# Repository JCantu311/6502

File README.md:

# 6502
Writing code for the W65C02 microprocessor.

## Links
[Compiler Project](COMPILER.md)

## Experimentation
The project root is dedicated to writing code for testing. The Computer Code subdirectory is for designing code for a custom computer I am designing, while the Computer Designs subdirectory is for the computer itself (including peripherals and extra hardware).

## Designing
The Computer I am designing is purely experimental and is (at the time of writing) far from production.

Further updates in the future could possibly result in a for-production product.

The Computer Code subdirectory contains the source code for the version of MS Basic designed for the computer, the operating system/kernel, and wozmon as a system monitor.

I would not recommend using any of my source code as its very sloppy and written with little competence, however, if you do, you know where to find the terms of the license.

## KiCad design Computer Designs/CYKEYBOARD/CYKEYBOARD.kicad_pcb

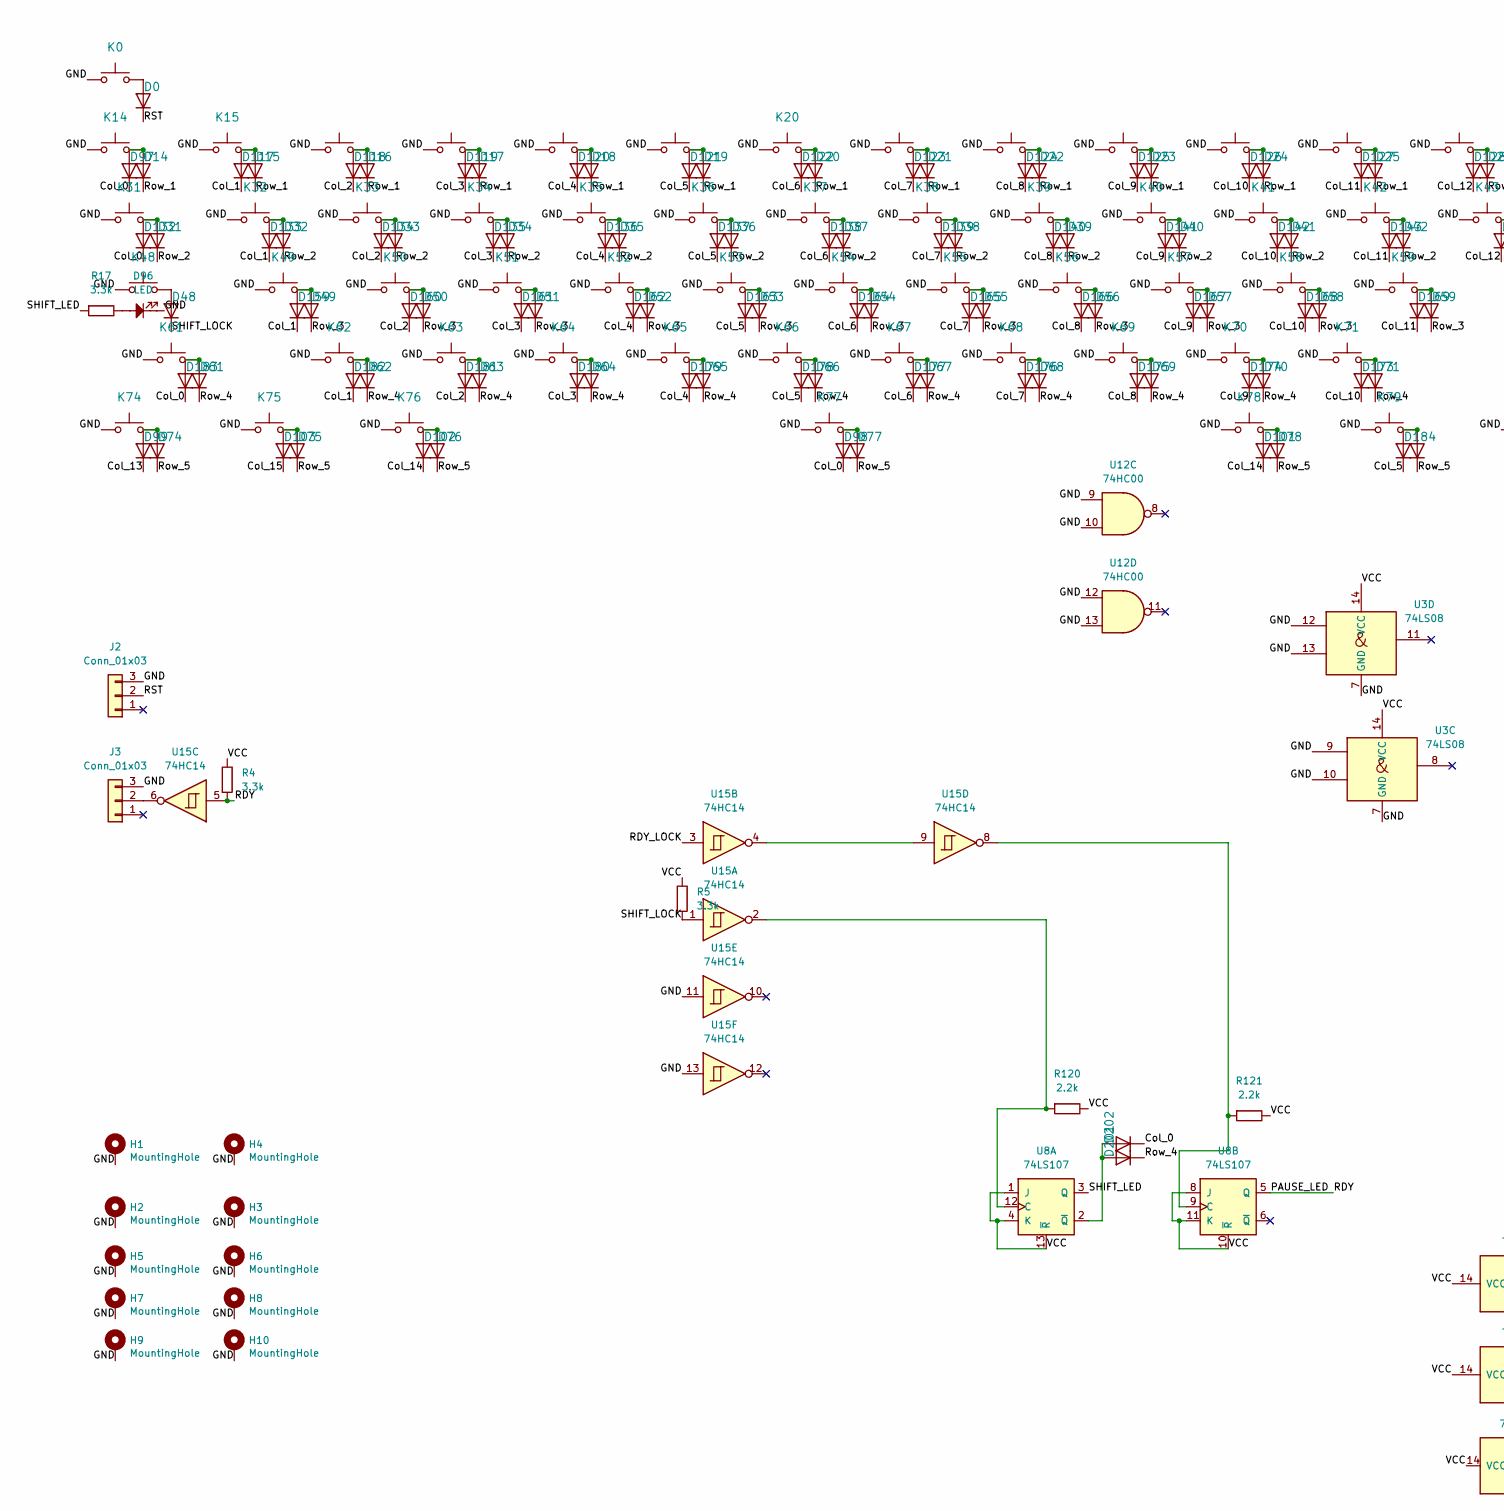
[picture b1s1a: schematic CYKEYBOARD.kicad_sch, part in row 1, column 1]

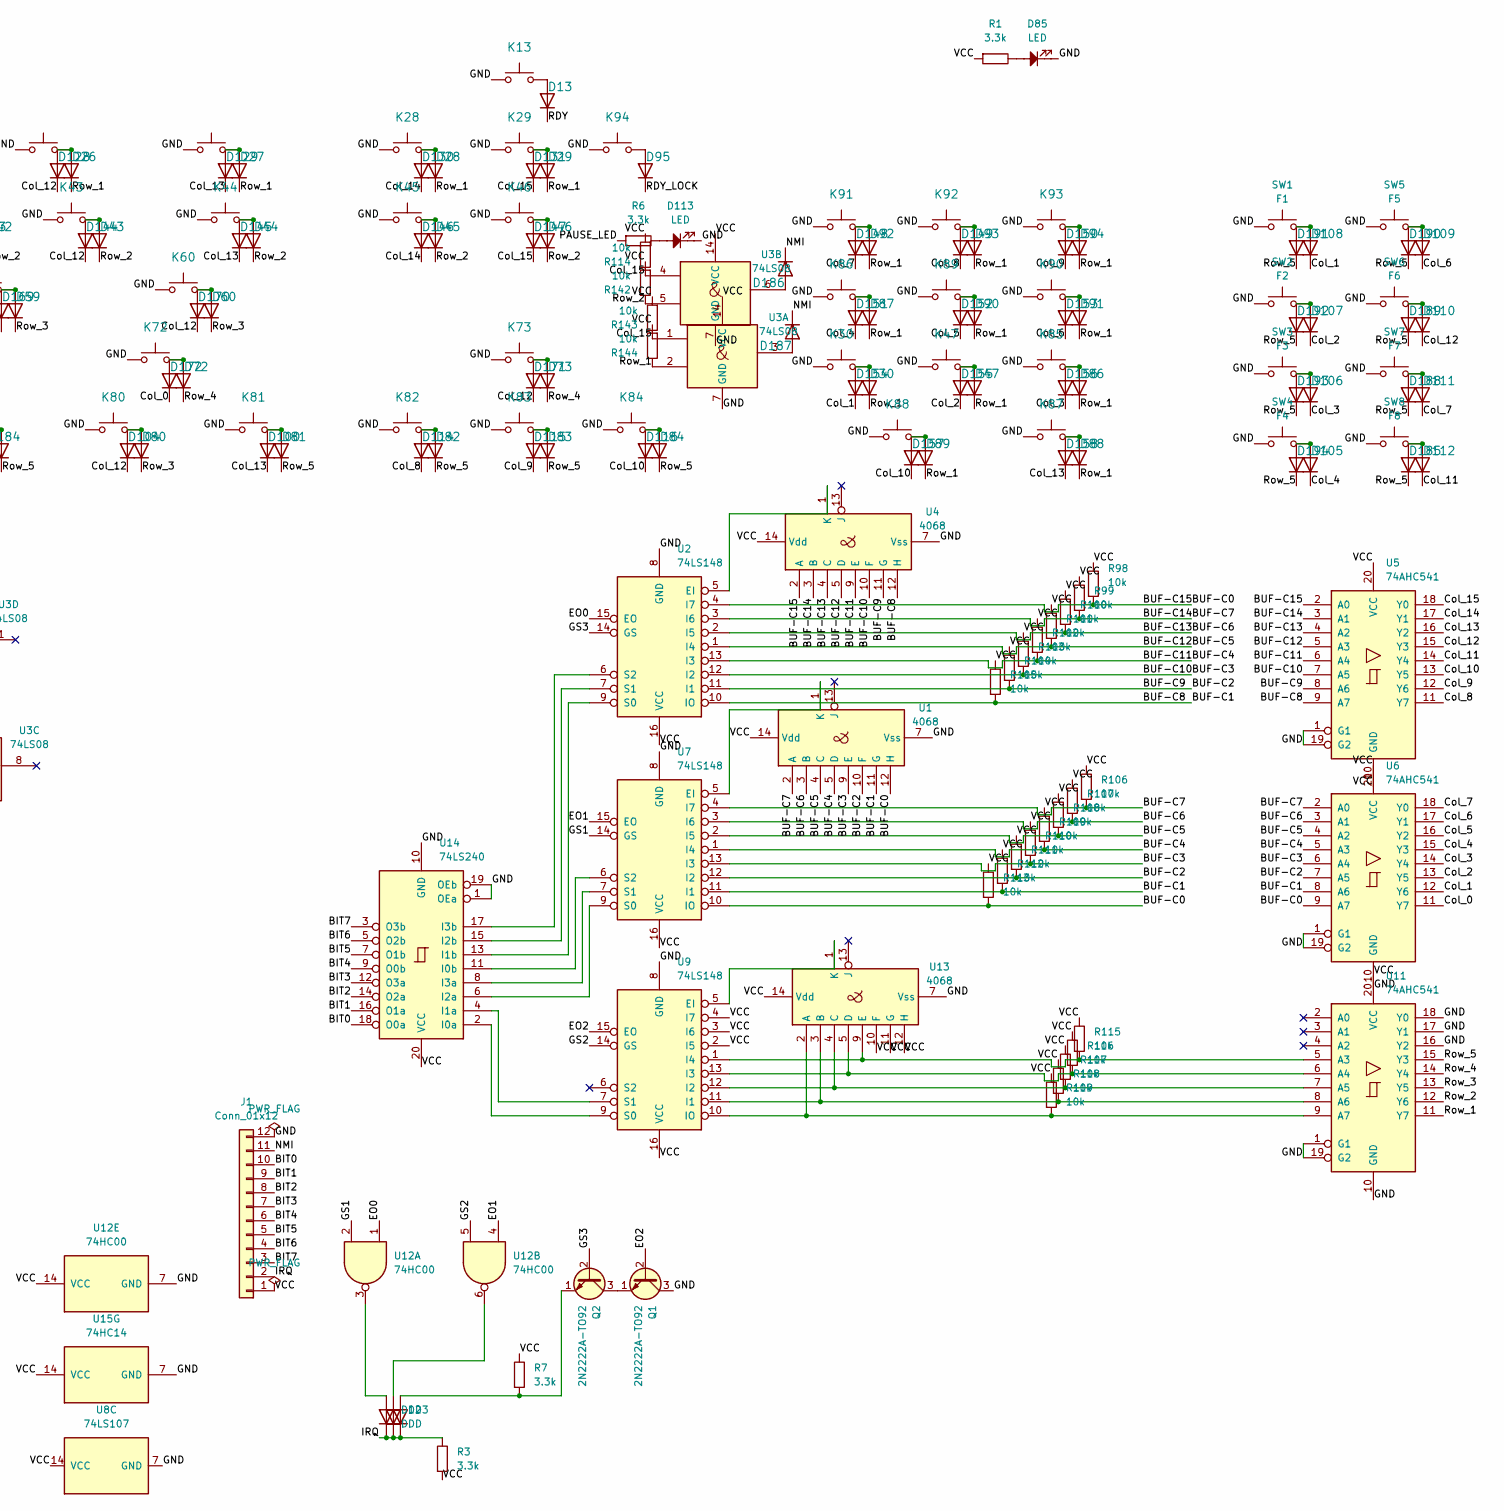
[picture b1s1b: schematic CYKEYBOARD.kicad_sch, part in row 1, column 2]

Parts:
D0, D13, D14, D15, D16, D17, D18, D19, D20, D21, D22, D23, D24, D25, D26, D27, D28, D29, D30, D31, D32, D33, D34, D35, D36, D37, D38, D39, D40, D41, D42, D43, D44, D45, D46, D47, D48, D49, D50, D51, D52, D53, D54, D55, D56, D57, D58, D59, D60, D61, D62, D63, D64, D65, D66, D67, D68, D69, D70, D71, D72, D73, D74, D75, D76, D77, D78, D79, D80, D81, D82, D83, D84, D86, D87, D88, D89, D90, D91, D92, D93, D94, D95, D97, D98, D99, D100, D101, D102, D103, D104, D105, D106, D107, D108, D109, D110, D111, D112, D114, D115, D116, D117, D118, D119, D120, D121, D122, D123, D124, D125, D126, D127, D128, D129, D130, D131, D132, D133, D134, D135, D136, D137, D138, D139, D140, D141, D142, D143, D144, D145, D146, D147, D148, D149, D150, D151, D152, D153, D154, D155, D156, D157, D158, D159, D160, D161, D162, D163, D164, D165, D166, D167, D168, D169, D170, D171, D172, D173, D174, D175, D176, D177, D178, D179, D180, D181, D182, D183, D184, D185, D186, D187, D188, D189, D190, D191, D192, D193, D194, D201, D202: D; D_T-1_P5.08mm_Horizontal
D1, D2, D3: D; D_DO-35_SOD27_P7.62mm_Horizontal
D85, D96, D113: LED; LED_D5.0mm
H1, H2, H3, H4, H5, H6, H7, H8, H9, H10: MountingHole; MountingHole_2.2mm_M2_Pad_Via
J1: Conn_01x12; PinHeader_1x12_P2.54mm_Vertical
J2, J3: Conn_01x03; FanPinHeader_1x03_P2.54mm_Vertical
K0: RESET; SW_Cherry_MX_1.00u_PCB
K13: READY; SW_Cherry_MX_2.75u_PCB
K14: ~~,,,,,,`; SW_Cherry_MX_1.00u_PCB
K15, K30: !,,,,,,1; SW_Cherry_MX_1.00u_PCB
K16, K47: @,,,,,,2; SW_Cherry_MX_1.00u_PCB
K17, K85: #,,,,,,3; SW_Cherry_MX_1.00u_PCB
K18, K86: $,,,,,,4; SW_Cherry_MX_1.00u_PCB
K19, K89: %,,,,,,5; SW_Cherry_MX_1.00u_PCB
K20, K90: ^,,,,,,6; SW_Cherry_MX_1.00u_PCB
K21, K91: &,,,,,,7; SW_Cherry_MX_1.00u_PCB
K22, K92: *,,,,,,8; SW_Cherry_MX_1.00u_PCB
K23, K93: (,,,,,,9; SW_Cherry_MX_1.00u_PCB
K24: ),,,,,,0; SW_Cherry_MX_1.00u_PCB
K25: _,,,,,,-; SW_Cherry_MX_1.00u_PCB
K26: +,,,,,,=; SW_Cherry_MX_1.00u_PCB
K27: BACKSPACE; SW_Cherry_MX_2.00u_PCB
K28: HOME; SW_Cherry_MX_1.00u_PCB
K29: MON; SW_Cherry_MX_1.00u_PCB
K31: SAVE,,,,,,LOAD; SW_Cherry_MX_1.25u_PCB
K32: Q; SW_Cherry_MX_1.00u_PCB
K33: W; SW_Cherry_MX_1.00u_PCB
K34: E; SW_Cherry_MX_1.00u_PCB
K35: R; SW_Cherry_MX_1.00u_PCB
K36: T; SW_Cherry_MX_1.00u_PCB
K37: Y; SW_Cherry_MX_1.00u_PCB
K38: U; SW_Cherry_MX_1.00u_PCB
K39: I; SW_Cherry_MX_1.00u_PCB
K40: O; SW_Cherry_MX_1.00u_PCB
K41: P; SW_Cherry_MX_1.00u_PCB
K42: {,,,,,,[; SW_Cherry_MX_1.00u_PCB
K43: },,,,,,]; SW_Cherry_MX_1.00u_PCB
K44: |,,,,,,\; SW_Cherry_MX_1.75u_PCB
K45: DEL; SW_Cherry_MX_1.00u_PCB
K46: BAS; SW_Cherry_MX_1.00u_PCB
K48: SHIFT,,,,,,LOCK; SW_Cherry_MX_1.50u_PCB
K49: A; SW_Cherry_MX_1.00u_PCB
K50: S; SW_Cherry_MX_1.00u_PCB
K51: D; SW_Cherry_MX_1.00u_PCB
K52: F; SW_Cherry_MX_1.00u_PCB
K53: G; SW_Cherry_MX_1.00u_PCB
K54: H; SW_Cherry_MX_1.00u_PCB
K55: J; SW_Cherry_MX_1.00u_PCB
K56: K; SW_Cherry_MX_1.00u_PCB
K57: L; SW_Cherry_MX_1.00u_PCB
K58: :,,,,,,;; SW_Cherry_MX_1.00u_PCB
K59: ",,,,,,'; SW_Cherry_MX_1.00u_PCB
K60: ENTER; SW_Cherry_MX_2.25u_PCB
K61: SHIFT; SW_Cherry_MX_2.00u_PCB
K62: Z; SW_Cherry_MX_1.00u_PCB
K63: X; SW_Cherry_MX_1.00u_PCB
K64: C; SW_Cherry_MX_1.00u_PCB
K65: V; SW_Cherry_MX_1.00u_PCB
K66: B; SW_Cherry_MX_1.00u_PCB
K67: N; SW_Cherry_MX_1.00u_PCB
K68: M; SW_Cherry_MX_1.00u_PCB
K69: <,,,,,,,; SW_Cherry_MX_1.00u_PCB
K70: >,,,,,,.; SW_Cherry_MX_1.00u_PCB
K71: ?,,,,,,/; SW_Cherry_MX_1.00u_PCB
K72: SHIFT; SW_Cherry_MX_2.75u_PCB
K73: ^; SW_Cherry_MX_1.00u_PCB
K74, K81: CTRL; SW_Cherry_MX_1.25u_PCB
K75: CYKA,,,,,,TECH; SW_Cherry_MX_1.25u_PCB
K76, K78: ALT; SW_Cherry_MX_1.25u_PCB
K77: Blank; SW_Cherry_MX_6.25u_PCB
K79: FN; SW_Cherry_MX_1.25u_PCB
K80: SELECT; SW_Cherry_MX_1.25u_PCB
K82: <; SW_Cherry_MX_1.00u_PCB
K83: \/; SW_Cherry_MX_1.00u_PCB
K84: >; SW_Cherry_MX_1.00u_PCB
K87: BACKSPACE; SW_Cherry_MX_1.00u_PCB
K88: ),,,,,,0; SW_Cherry_MX_2.00u_PCB
K94: PAUSE; SW_Cherry_MX_1.00u_PCB
Q1, Q2: 2N2222A-TO92; TO-92_Inline_Wide_EBC
R1, R3, R4, R5, R6, R7, R17: 3.3k; R_Axial_DIN0207_L6.3mm_D2.5mm_P10.16mm_Horizontal
R98, R99, R100, R101, R102, R103, R104, R105, R106, R107, R108, R109, R110, R111, R112, R113, R114, R115, R116, R117, R118, R119, R142, R143, R144: 10k; R_Axial_DIN0207_L6.3mm_D2.5mm_P10.16mm_Horizontal
R120, R121: 2.2k; R_Axial_DIN0207_L6.3mm_D2.5mm_P10.16mm_Horizontal
SW1: F1; SW_Cherry_MX_2.00u_PCB
SW2: F2; SW_Cherry_MX_2.00u_PCB
SW3: F3; SW_Cherry_MX_2.00u_PCB
SW4: F4; SW_Cherry_MX_2.00u_PCB
SW5: F5; SW_Cherry_MX_2.00u_PCB
SW6: F6; SW_Cherry_MX_2.00u_PCB
SW7: F7; SW_Cherry_MX_2.00u_PCB
SW8: F8; SW_Cherry_MX_2.00u_PCB
U1, U4, U13: 4068; DIP-14_W7.62mm_Socket
U2, U7, U9: 74LS148; DIP-16_W7.62mm_Socket
U3: 74LS08; DIP-14_W7.62mm_Socket
U5, U6, U11: 74AHC541; DIP-20_W7.62mm_Socket
U8: 74LS107; DIP-14_W7.62mm_Socket
U12: 74HC00; DIP-14_W7.62mm_Socket
U14: 74LS240; DIP-20_W7.62mm_Socket
U15: 74HC14; DIP-14_W7.62mm_Socket

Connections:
/BIT0: J1.10, U14.18 (O0a)
/BIT1: J1.9, U14.16 (O1a)
/BIT2: J1.8, U14.14 (O2a)
/BIT3: J1.7, U14.12 (O3a)
/BIT4: J1.6, U14.9 (O0b)
/BIT5: J1.5, U14.7 (O1b)
/BIT6: J1.4, U14.5 (O2b)
/BIT7: J1.3, U14.3 (O3b)
/BUF-C0: R98.1, R113.1, U1.12 (H), U2.4 (I7), U4.2 (A), U5.2 (A0), U6.9 (A7), U7.10 (IO)
/BUF-C1: R105.1, R112.1, U1.11 (G), U2.10 (IO), U4.12 (H), U5.9 (A7), U6.8 (A6), U7.11 (I1)
/BUF-C2: R104.1, R111.1, U1.10 (F), U2.11 (I1), U4.11 (G), U5.8 (A6), U6.7 (A5), U7.12 (I2)
/BUF-C10: R103.1, R110.1, U1.9 (E), U2.12 (I2), U4.10 (F), U5.7 (A5), U6.6 (A4), U7.13 (I3)
/BUF-C11: R102.1, R109.1, U1.5 (D), U2.13 (I3), U4.9 (E), U5.6 (A4), U6.5 (A3), U7.1 (I4)
/BUF-C12: R101.1, R108.1, U1.4 (C), U2.1 (I4), U4.5 (D), U5.5 (A3), U6.4 (A2), U7.2 (I5)
/BUF-C13: R100.1, R107.1, U1.3 (B), U2.2 (I5), U4.4 (C), U5.4 (A2), U6.3 (A1), U7.3 (I6)
/BUF-C14: R99.1, R106.1, U1.2 (A), U2.3 (I6), U4.3 (B), U5.3 (A1), U6.2 (A0), U7.4 (I7)
/Col_0: D97.1 (K), D98.1 (K), D132.1 (K), D172.1 (K), D183.1 (K), D202.1 (K), U6.11 (Y7)
/Col_1: D108.1 (K), D117.1 (K), D133.1 (K), D154.1 (K), D159.1 (K), D182.1 (K), U6.12 (Y6)
/Col_2: D107.1 (K), D118.1 (K), D134.1 (K), D155.1 (K), D160.1 (K), D181.1 (K), U6.13 (Y5)
/Col_3: D106.1 (K), D119.1 (K), D135.1 (K), D156.1 (K), D161.1 (K), D180.1 (K), U6.14 (Y4)
/Col_4: D105.1 (K), D120.1 (K), D136.1 (K), D151.1 (K), D162.1 (K), D179.1 (K), U6.15 (Y3)
/Col_5: D121.1 (K), D137.1 (K), D152.1 (K), D163.1 (K), D178.1 (K), D184.1 (K), U6.16 (Y2)
/Col_6: D109.1 (K), D122.1 (K), D138.1 (K), D153.1 (K), D164.1 (K), D177.1 (K), U6.17 (Y1)
/Col_7: D111.1 (K), D123.1 (K), D139.1 (K), D148.1 (K), D165.1 (K), D176.1 (K), U6.18 (Y0)
/Col_8: D114.1 (K), D124.1 (K), D140.1 (K), D149.1 (K), D166.1 (K), D175.1 (K), U5.11 (Y7)
/Col_9: D115.1 (K), D125.1 (K), D141.1 (K), D150.1 (K), D167.1 (K), D174.1 (K), U5.12 (Y6)
/Col_10: D116.1 (K), D126.1 (K), D142.1 (K), D157.1 (K), D168.1 (K), D173.1 (K), U5.13 (Y5)
/Col_11: D112.1 (K), D127.1 (K), D143.1 (K), D169.1 (K), U5.14 (Y4)
/Col_12: D104.1 (K), D110.1 (K), D128.1 (K), D144.1 (K), D170.1 (K), D171.1 (K), U5.15 (Y3)
/Col_13: D99.1 (K), D100.1 (K), D129.1 (K), D145.1 (K), D158.1 (K), U5.16 (Y2)
/Col_14: D101.1 (K), D102.1 (K), D130.1 (K), D146.1 (K), U5.17 (Y1)
/Col_15: D103.1 (K), D131.1 (K), D147.1 (K), R114.2, R143.2, U3.1, U3.4, U5.18 (Y0)
/EO0: U2.15 (EO), U12.1
/EO1: U7.15 (EO), U12.4
/EO2: Q1.2 (B), U9.15 (EO)
/GND: D85.1, D96.1, D113.1, H1.1 (1_1), H2.1 (1_1), H3.1 (1_1), H4.1 (1_1), H5.1 (1_1), H6.1 (1_1), H7.1 (1_1), H8.1 (1_1), H9.1 (1_1), H10.1 (1_1), J1.12, J2.3, J3.3, K0.1, K13.1, K14.1, K15.1, K16.1, K17.1, K18.1, K19.1, K20.1, K21.1, K22.1, K23.1, K24.1, K25.1, K26.1, K27.1, K28.1, K29.1, K30.1, K31.1, K32.1, K33.1, K34.1, K35.1, K36.1, K37.1, K38.1, K39.1, K40.1, K41.1, K42.1, K43.1, K44.1, K45.1, K46.1, K47.1, K48.1, K49.1, K50.1, K51.1, K52.1, K53.1, K54.1, K55.1, K56.1, K57.1, K58.1, K59.1, K60.1, K61.1, K62.1, K63.1, K64.1, K65.1, K66.1, K67.1, K68.1, K69.1, K70.1, K71.1, K72.1, K73.1, K74.1, K75.1, K76.1, K77.1, K78.1, K79.1, K80.1, K81.1, K82.1, K83.1, K84.1, K85.1, K86.1, K87.1, K88.1, K89.1, K90.1, K91.1, K92.1, K93.1, K94.1, Q1.3 (C), SW1.1, SW2.1, SW3.1, SW4.1, SW5.1, SW6.1, SW7.1, SW8.1, U1.7 (Vss), U2.8 (GND), U3.7 (GND), U3.9, U3.10, U3.12, U3.13, U4.7 (Vss), U5.1 (G1), U5.19 (G2), U6.1 (G1), U6.10 (GND), U6.19 (G2), U7.8 (GND), U8.7 (GND), U9.8 (GND), U11.1 (G1), U11.10 (GND), U11.16 (Y2), U11.17 (Y1), U11.18 (Y0), U11.19 (G2), U12.7 (GND), U12.9, U12.10, U12.12, U12.13, U13.7 (Vss), U14.1 (OEa), U14.10 (GND), U14.19 (OEb), U15.7 (GND), U15.11, U15.13
/GS1: U7.14 (GS), U12.2
/GS2: U9.14 (GS), U12.5
/GS3: Q2.2 (B), U2.14 (GS)
/IRQ: D1.1 (K), D2.1 (K), D3.1 (K), J1.2, R3.2
/NMI: D186.1 (K), D187.1 (K), J1.11
/PAUSE_LED: D13.1 (K), R4.1, R6.1, U8.5 (Q), U15.5
/RDY_LOCK: D95.1 (K), U15.3
/RST: D0.1 (K), J2.2
/Row_1: D14.1 (K), D15.1 (K), D16.1 (K), D17.1 (K), D18.1 (K), D19.1 (K), D20.1 (K), D21.1 (K), D22.1 (K), D23.1 (K), D24.1 (K), D25.1 (K), D26.1 (K), D27.1 (K), D28.1 (K), D29.1 (K), D30.1 (K), D47.1 (K), D86.1 (K), D87.1 (K), D88.1 (K), D89.1 (K), D90.1 (K), D91.1 (K), D92.1 (K), D93.1 (K), D94.1 (K), R144.2, U3.2, U11.11 (Y7)
/Row_2: D31.1 (K), D32.1 (K), D33.1 (K), D34.1 (K), D35.1 (K), D36.1 (K), D37.1 (K), D38.1 (K), D39.1 (K), D40.1 (K), D41.1 (K), D42.1 (K), D43.1 (K), D44.1 (K), D45.1 (K), D46.1 (K), R142.2, U3.5, U11.12 (Y6)
/Row_3: D49.1 (K), D50.1 (K), D51.1 (K), D52.1 (K), D53.1 (K), D54.1 (K), D55.1 (K), D56.1 (K), D57.1 (K), D58.1 (K), D59.1 (K), D60.1 (K), D80.1 (K), U11.13 (Y5)
/Row_4: D61.1 (K), D62.1 (K), D63.1 (K), D64.1 (K), D65.1 (K), D66.1 (K), D67.1 (K), D68.1 (K), D69.1 (K), D70.1 (K), D71.1 (K), D72.1 (K), D73.1 (K), D201.1 (K), U11.14 (Y4)
/Row_5: D74.1 (K), D75.1 (K), D76.1 (K), D77.1 (K), D78.1 (K), D79.1 (K), D81.1 (K), D82.1 (K), D83.1 (K), D84.1 (K), D185.1 (K), D188.1 (K), D189.1 (K), D190.1 (K), D191.1 (K), D192.1 (K), D193.1 (K), D194.1 (K), U11.15 (Y3)
/SHIFT_LED: R17.1, U8.3 (Q)
/SHIFT_LOCK: D48.1 (K), R5.1, U15.1
/VCC: J1.1, R1.1, R3.1, R4.2, R5.2, R7.2, R98.2, R99.2, R100.2, R101.2, R102.2, R103.2, R104.2, R105.2, R106.2, R107.2, R108.2, R109.2, R110.2, R111.2, R112.2, R113.2, R114.1, R115.2, R116.2, R117.2, R118.2, R119.2, R120.2, R121.2, R142.1, R143.1, R144.1, U1.14 (Vdd), U2.16 (VCC), U3.14 (VCC), U4.14 (Vdd), U5.10 (GND), U5.20 (VCC), U6.20 (VCC), U7.16 (VCC), U8.1 (J), U8.4 (K), U8.8 (J), U8.10 (~R), U8.11 (K), U8.13 (~R), U8.14 (VCC), U9.2 (I5), U9.3 (I6), U9.4 (I7), U9.16 (VCC), U11.20 (VCC), U12.14 (VCC), U13.10 (F), U13.11 (G), U13.12 (H), U13.14 (Vdd), U14.20 (VCC), U15.14 (VCC)
unnamed: D0.2 (A), K0.2
unnamed: D1.2 (A), U12.3
unnamed: D2.2 (A), U12.6
unnamed: D3.2 (A), Q2.1 (E), R7.1
unnamed: D13.2 (A), K13.2
unnamed: D14.2 (A), D97.2 (A), K14.2
unnamed: D48.2 (A), K48.2
unnamed: D74.2 (A), D99.2 (A), K74.2
unnamed: D77.2 (A), D98.2 (A), K77.2
unnamed: D85.2, R1.2
unnamed: D95.2 (A), K94.2
unnamed: D96.2, R17.2
unnamed: D81.2 (A), D100.2 (A), K81.2
unnamed: D78.2 (A), D101.2 (A), K78.2
unnamed: D76.2 (A), D102.2 (A), K76.2
unnamed: D75.2 (A), D103.2 (A), K75.2
unnamed: D80.2 (A), D104.2 (A), K80.2
unnamed: D105.2 (A), D194.2 (A), SW4.2
unnamed: D106.2 (A), D193.2 (A), SW3.2
unnamed: D107.2 (A), D192.2 (A), SW2.2
unnamed: D108.2 (A), D191.2 (A), SW1.2
unnamed: D109.2 (A), D190.2 (A), SW5.2
unnamed: D110.2 (A), D189.2 (A), SW6.2
unnamed: D111.2 (A), D188.2 (A), SW7.2
unnamed: D112.2 (A), D185.2 (A), SW8.2
unnamed: D113.2, R6.2
unnamed: D82.2 (A), D114.2 (A), K82.2
unnamed: D83.2 (A), D115.2 (A), K83.2
unnamed: D84.2 (A), D116.2 (A), K84.2
unnamed: D15.2 (A), D117.2 (A), K15.2
unnamed: D16.2 (A), D118.2 (A), K16.2
unnamed: D17.2 (A), D119.2 (A), K17.2
unnamed: D18.2 (A), D120.2 (A), K18.2
unnamed: D19.2 (A), D121.2 (A), K19.2
unnamed: D20.2 (A), D122.2 (A), K20.2
unnamed: D21.2 (A), D123.2 (A), K21.2
unnamed: D22.2 (A), D124.2 (A), K22.2
unnamed: D23.2 (A), D125.2 (A), K23.2
unnamed: D24.2 (A), D126.2 (A), K24.2
unnamed: D25.2 (A), D127.2 (A), K25.2
unnamed: D26.2 (A), D128.2 (A), K26.2
unnamed: D27.2 (A), D129.2 (A), K27.2
unnamed: D28.2 (A), D130.2 (A), K28.2
unnamed: D29.2 (A), D131.2 (A), K29.2
unnamed: D31.2 (A), D132.2 (A), K31.2
unnamed: D32.2 (A), D133.2 (A), K32.2
unnamed: D33.2 (A), D134.2 (A), K33.2
unnamed: D34.2 (A), D135.2 (A), K34.2
unnamed: D35.2 (A), D136.2 (A), K35.2
unnamed: D36.2 (A), D137.2 (A), K36.2
unnamed: D37.2 (A), D138.2 (A), K37.2
unnamed: D38.2 (A), D139.2 (A), K38.2
unnamed: D39.2 (A), D140.2 (A), K39.2
unnamed: D40.2 (A), D141.2 (A), K40.2
unnamed: D41.2 (A), D142.2 (A), K41.2
unnamed: D42.2 (A), D143.2 (A), K42.2
unnamed: D43.2 (A), D144.2 (A), K43.2
unnamed: D44.2 (A), D145.2 (A), K44.2
unnamed: D45.2 (A), D146.2 (A), K45.2
unnamed: D46.2 (A), D147.2 (A), K46.2
unnamed: D92.2 (A), D148.2 (A), K91.2
unnamed: D93.2 (A), D149.2 (A), K92.2
unnamed: D94.2 (A), D150.2 (A), K93.2
unnamed: D87.2 (A), D151.2 (A), K86.2
unnamed: D90.2 (A), D152.2 (A), K89.2
unnamed: D91.2 (A), D153.2 (A), K90.2
unnamed: D30.2 (A), D154.2 (A), K30.2
unnamed: D47.2 (A), D155.2 (A), K47.2
unnamed: D86.2 (A), D156.2 (A), K85.2
unnamed: D89.2 (A), D157.2 (A), K88.2
unnamed: D88.2 (A), D158.2 (A), K87.2
unnamed: D49.2 (A), D159.2 (A), K49.2
unnamed: D50.2 (A), D160.2 (A), K50.2
unnamed: D51.2 (A), D161.2 (A), K51.2
unnamed: D52.2 (A), D162.2 (A), K52.2
unnamed: D53.2 (A), D163.2 (A), K53.2
unnamed: D54.2 (A), D164.2 (A), K54.2
unnamed: D55.2 (A), D165.2 (A), K55.2
unnamed: D56.2 (A), D166.2 (A), K56.2
unnamed: D57.2 (A), D167.2 (A), K57.2
unnamed: D58.2 (A), D168.2 (A), K58.2
unnamed: D59.2 (A), D169.2 (A), K59.2
unnamed: D60.2 (A), D170.2 (A), K60.2
unnamed: D73.2 (A), D171.2 (A), K73.2
unnamed: D72.2 (A), D172.2 (A), K72.2
unnamed: D71.2 (A), D173.2 (A), K71.2
unnamed: D70.2 (A), D174.2 (A), K70.2
unnamed: D69.2 (A), D175.2 (A), K69.2
unnamed: D68.2 (A), D176.2 (A), K68.2
unnamed: D67.2 (A), D177.2 (A), K67.2
unnamed: D66.2 (A), D178.2 (A), K66.2
unnamed: D65.2 (A), D179.2 (A), K65.2
unnamed: D64.2 (A), D180.2 (A), K64.2
unnamed: D63.2 (A), D181.2 (A), K63.2
unnamed: D62.2 (A), D182.2 (A), K62.2
unnamed: D61.2 (A), D183.2 (A), K61.2
unnamed: D79.2 (A), D184.2 (A), K79.2
unnamed: D186.2 (A), U3.6
unnamed: D187.2 (A), U3.3
unnamed: D201.2 (A), D202.2 (A), U8.2 (~Q)
unnamed: J3.2, U15.6
unnamed: Q1.1 (E), Q2.3 (C)
unnamed: U1.1 (K), U7.5 (EI)
unnamed: U2.5 (EI), U4.1 (K)
unnamed: R120.1, U8.12 (C), U15.2
unnamed: R121.1, U8.9 (C), U15.8
unnamed: R115.1, U9.1 (I4), U11.5 (A3), U13.9 (E)
unnamed: R116.1, U9.13 (I3), U11.6 (A4), U13.5 (D)
unnamed: R117.1, U9.12 (I2), U11.7 (A5), U13.4 (C)
unnamed: R118.1, U9.11 (I1), U11.8 (A6), U13.3 (B)
unnamed: R119.1, U9.10 (IO), U11.9 (A7), U13.2 (A)
unnamed: U9.5 (EI), U13.1 (K)
unnamed: U9.9 (S0), U14.2 (I0a)
unnamed: U7.6 (S2), U14.11 (I0b)
unnamed: U9.7 (S1), U14.4 (I1a)
unnamed: U2.9 (S0), U14.13 (I1b)
unnamed: U7.9 (S0), U14.6 (I2a)
unnamed: U2.7 (S1), U14.15 (I2b)
unnamed: U7.7 (S1), U14.8 (I3a)
unnamed: U2.6 (S2), U14.17 (I3b)
unnamed: U15.4, U15.9

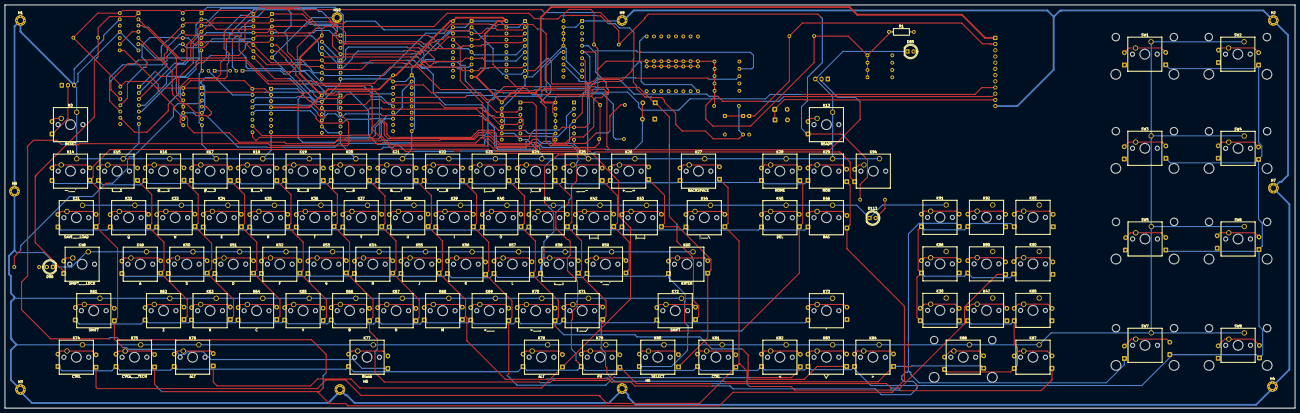
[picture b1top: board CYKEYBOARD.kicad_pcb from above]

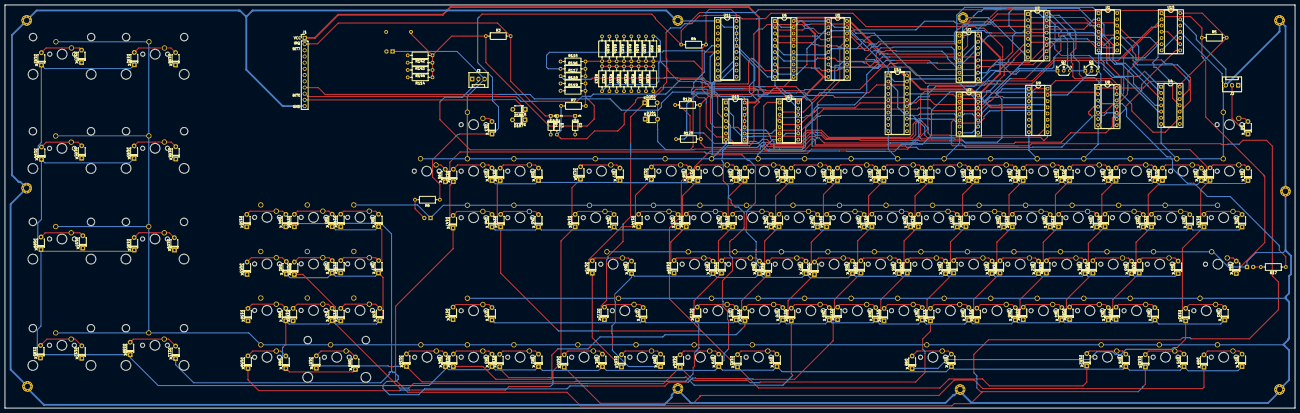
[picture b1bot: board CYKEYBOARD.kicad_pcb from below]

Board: 2 copper layers, 528.3 x 165.1 mm, 342 parts (237 on the bottom side), 173 nets.

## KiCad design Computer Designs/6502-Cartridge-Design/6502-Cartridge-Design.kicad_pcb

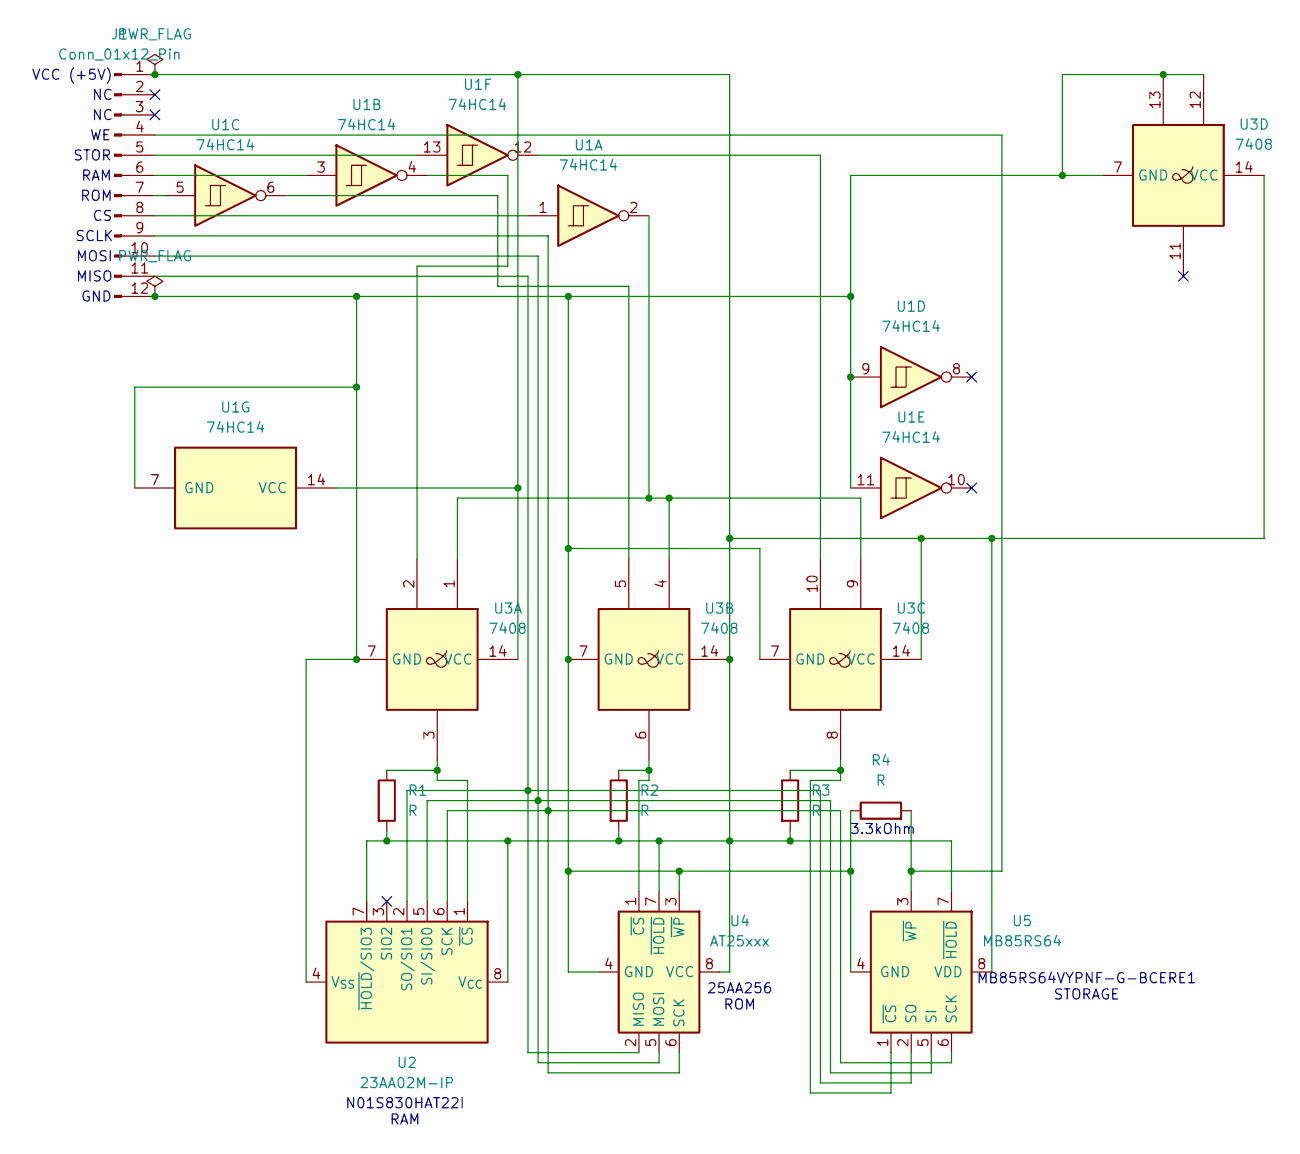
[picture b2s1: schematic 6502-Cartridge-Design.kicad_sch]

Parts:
J1: Conn_01x12_Pin; Cartridge Pads
R1, R2, R3, R4: R; R_Axial_DIN0204_L3.6mm_D1.6mm_P5.08mm_Horizontal
U1: 74HC14; DIP-14_W7.62mm
U2: 23AA02M-IP; TSSOP-8_4.4x3mm_P0.65mm
U3: 7408; DIP-14_W7.62mm
U4: AT25xxx; DIP-8_W7.62mm
U5: MB85RS64; SOIC-8_3.9x4.9mm_P1.27mm

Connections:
unnamed: J1.1, R1.2, R2.2, R3.2, U1.14 (VCC), U2.7 (~HOLD/SIO3), U2.8 (V_{CC}), U3.14 (VCC), U4.7 (~HOLD), U4.8 (VCC), U5.7 (~HOLD), U5.8 (VDD)
unnamed: J1.4, R4.2, U5.3 (~WP)
unnamed: J1.5, U1.13
unnamed: J1.6, U1.3
unnamed: J1.7, U1.5
unnamed: J1.8, U1.1
unnamed: J1.9, U2.6 (SCK), U4.6 (SCK), U5.6 (SCK)
unnamed: J1.10, U2.5 (SI/SIO0), U4.5 (MOSI), U5.5 (SI)
unnamed: J1.11, U2.2 (SO/SIO1), U4.2 (MISO), U5.2 (SO)
unnamed: J1.12, R4.1, U1.7 (GND), U1.9, U1.11, U2.4 (V_{SS}), U3.7 (GND), U3.12, U3.13, U4.3 (~WP), U4.4 (GND), U5.4 (GND)
unnamed: U1.2, U3.1, U3.4, U3.9
unnamed: U1.4, U3.2
unnamed: U1.6, U3.5
unnamed: U1.12, U3.10
unnamed: R1.1, U2.1 (~CS), U3.3
unnamed: R2.1, U3.6, U4.1 (~CS)
unnamed: R3.1, U3.8, U5.1 (~CS)

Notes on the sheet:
MOSI
STOR
ROM
MB85RS64VYPNF-G-BCERE1 STORAGE
MISO
N01S830HAT22I RAM
SCLK
VCC (+5V)
3.3kOhm
GND
RAM
25AA256 ROM

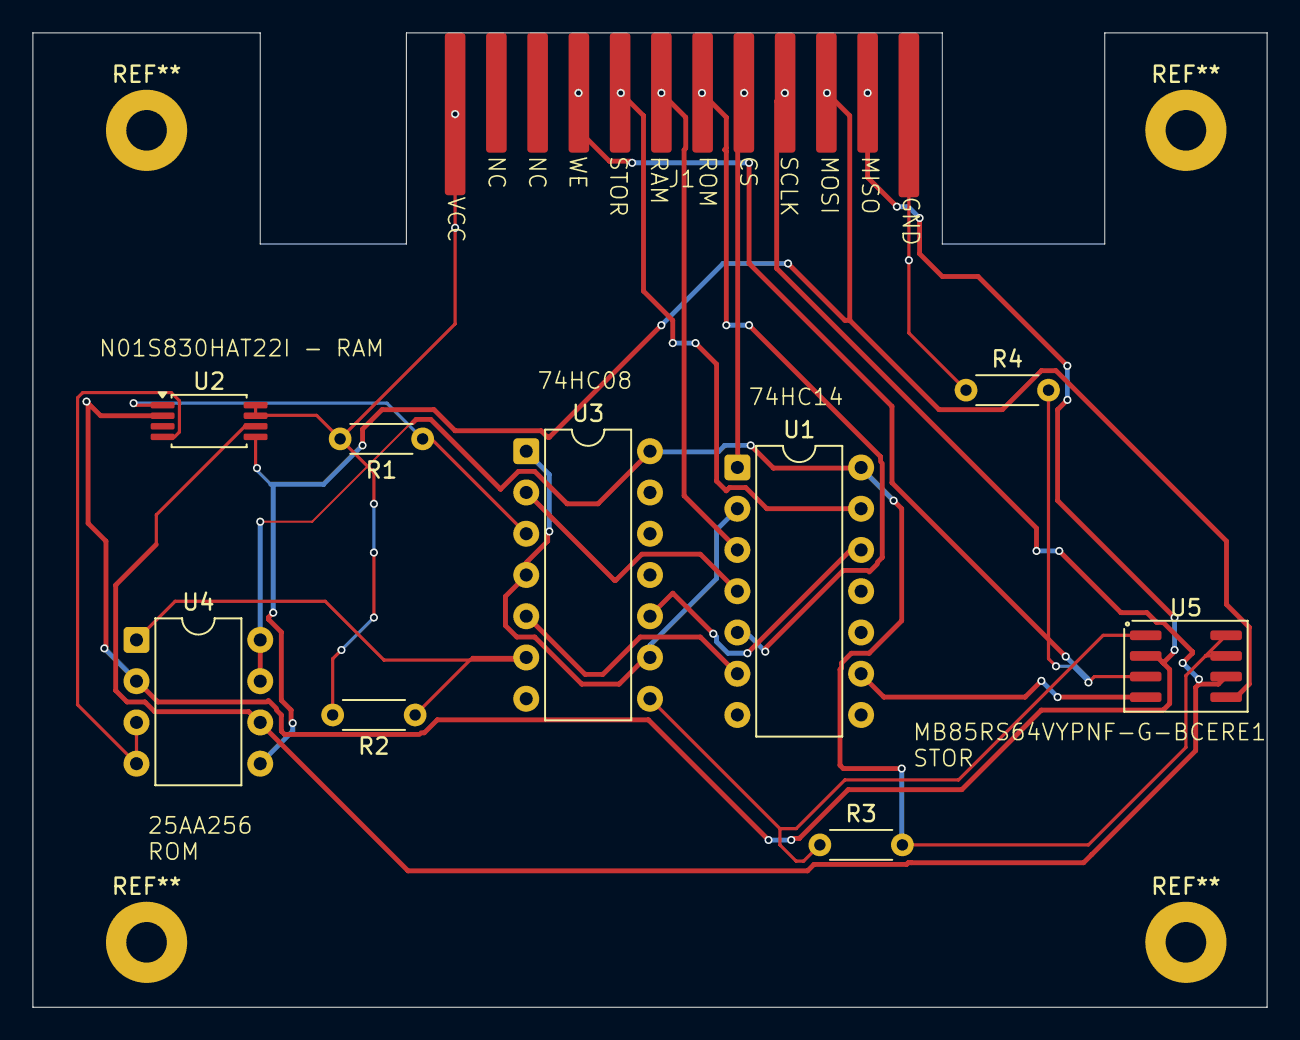
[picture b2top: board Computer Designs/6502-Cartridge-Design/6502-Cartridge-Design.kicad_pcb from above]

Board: 2 copper layers, 76.0 x 60.0 mm, 10 parts (0 on the bottom side), 17 nets.

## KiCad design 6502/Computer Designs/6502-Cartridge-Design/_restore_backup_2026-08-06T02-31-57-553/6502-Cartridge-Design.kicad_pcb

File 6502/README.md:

# 6502
Writing code for the W65C02 microprocessor.

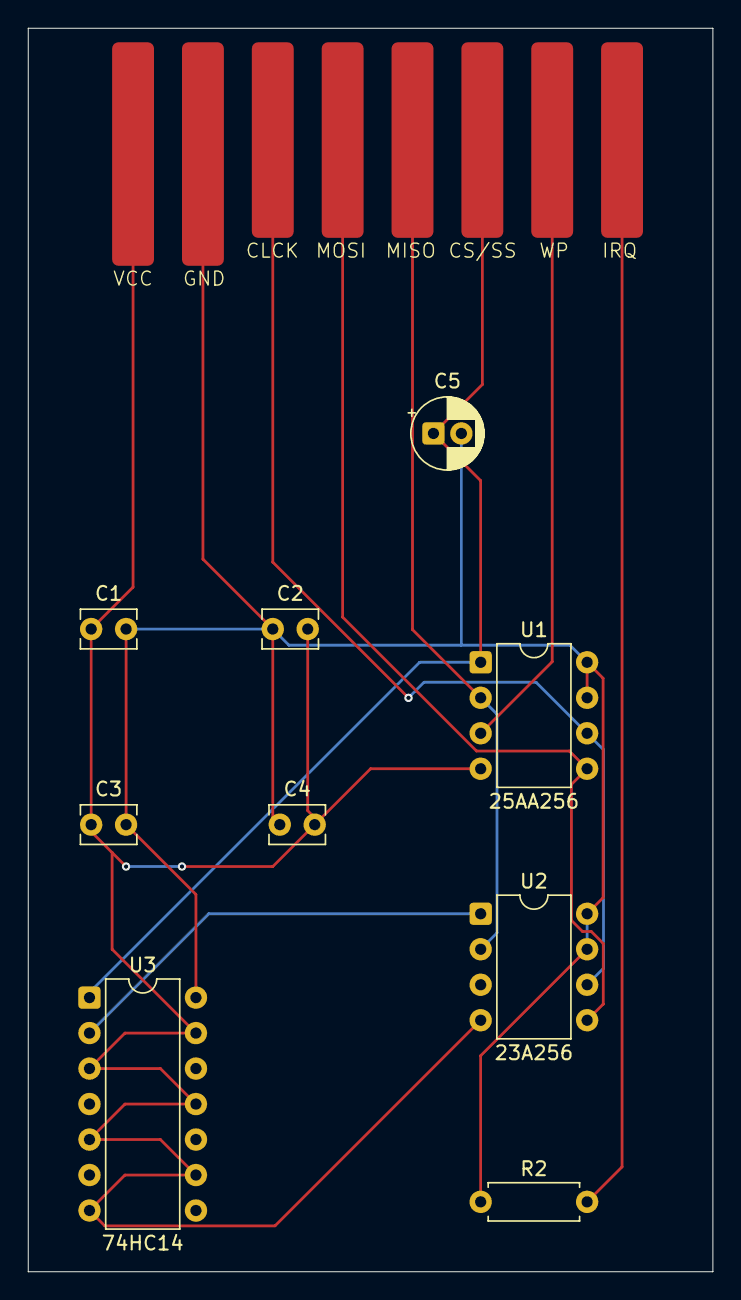
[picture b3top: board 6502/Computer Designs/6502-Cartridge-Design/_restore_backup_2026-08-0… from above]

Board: 2 copper layers, 49.0 x 89.0 mm, 9 parts (0 on the bottom side), 7 nets.

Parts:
C1, C2, C3, C4: C; C_Disc_D3.8mm_W2.6mm_P2.50mm
C5: C; CP_Radial_D5.0mm_P2.00mm
R2: R; R_Axial_DIN0207_L6.3mm_D2.5mm_P7.62mm_Horizontal
U1: 25AA256; DIP-8_W7.62mm
U2: 23A256; DIP-8_W7.62mm
U3: 74HC14; DIP-14_W7.62mm

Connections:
unnamed: C1.1, C2.2, C3.1, C4.2, U1.4 (GND), U2.4 (V_{SS}), U3.3, U3.5, U3.7 (GND), U3.9, U3.11, U3.13
unnamed: C1.2, C2.1, C3.2, C4.1, C5.2, R2.1, U1.7 (~HOLD), U1.8 (VCC), U2.7 (~HOLD/SIO3), U2.8 (V_{CC}), U3.14 (VCC)
unnamed: U1.6 (SCK), U2.6 (SCK)
unnamed: U1.5 (MOSI), U2.5 (SI/SIO0)
unnamed: U1.2 (MISO), U2.2 (SO/SIO1)
unnamed: C5.1, U1.1 (~CS), U3.1
unnamed: U2.1 (~CS), U3.2
